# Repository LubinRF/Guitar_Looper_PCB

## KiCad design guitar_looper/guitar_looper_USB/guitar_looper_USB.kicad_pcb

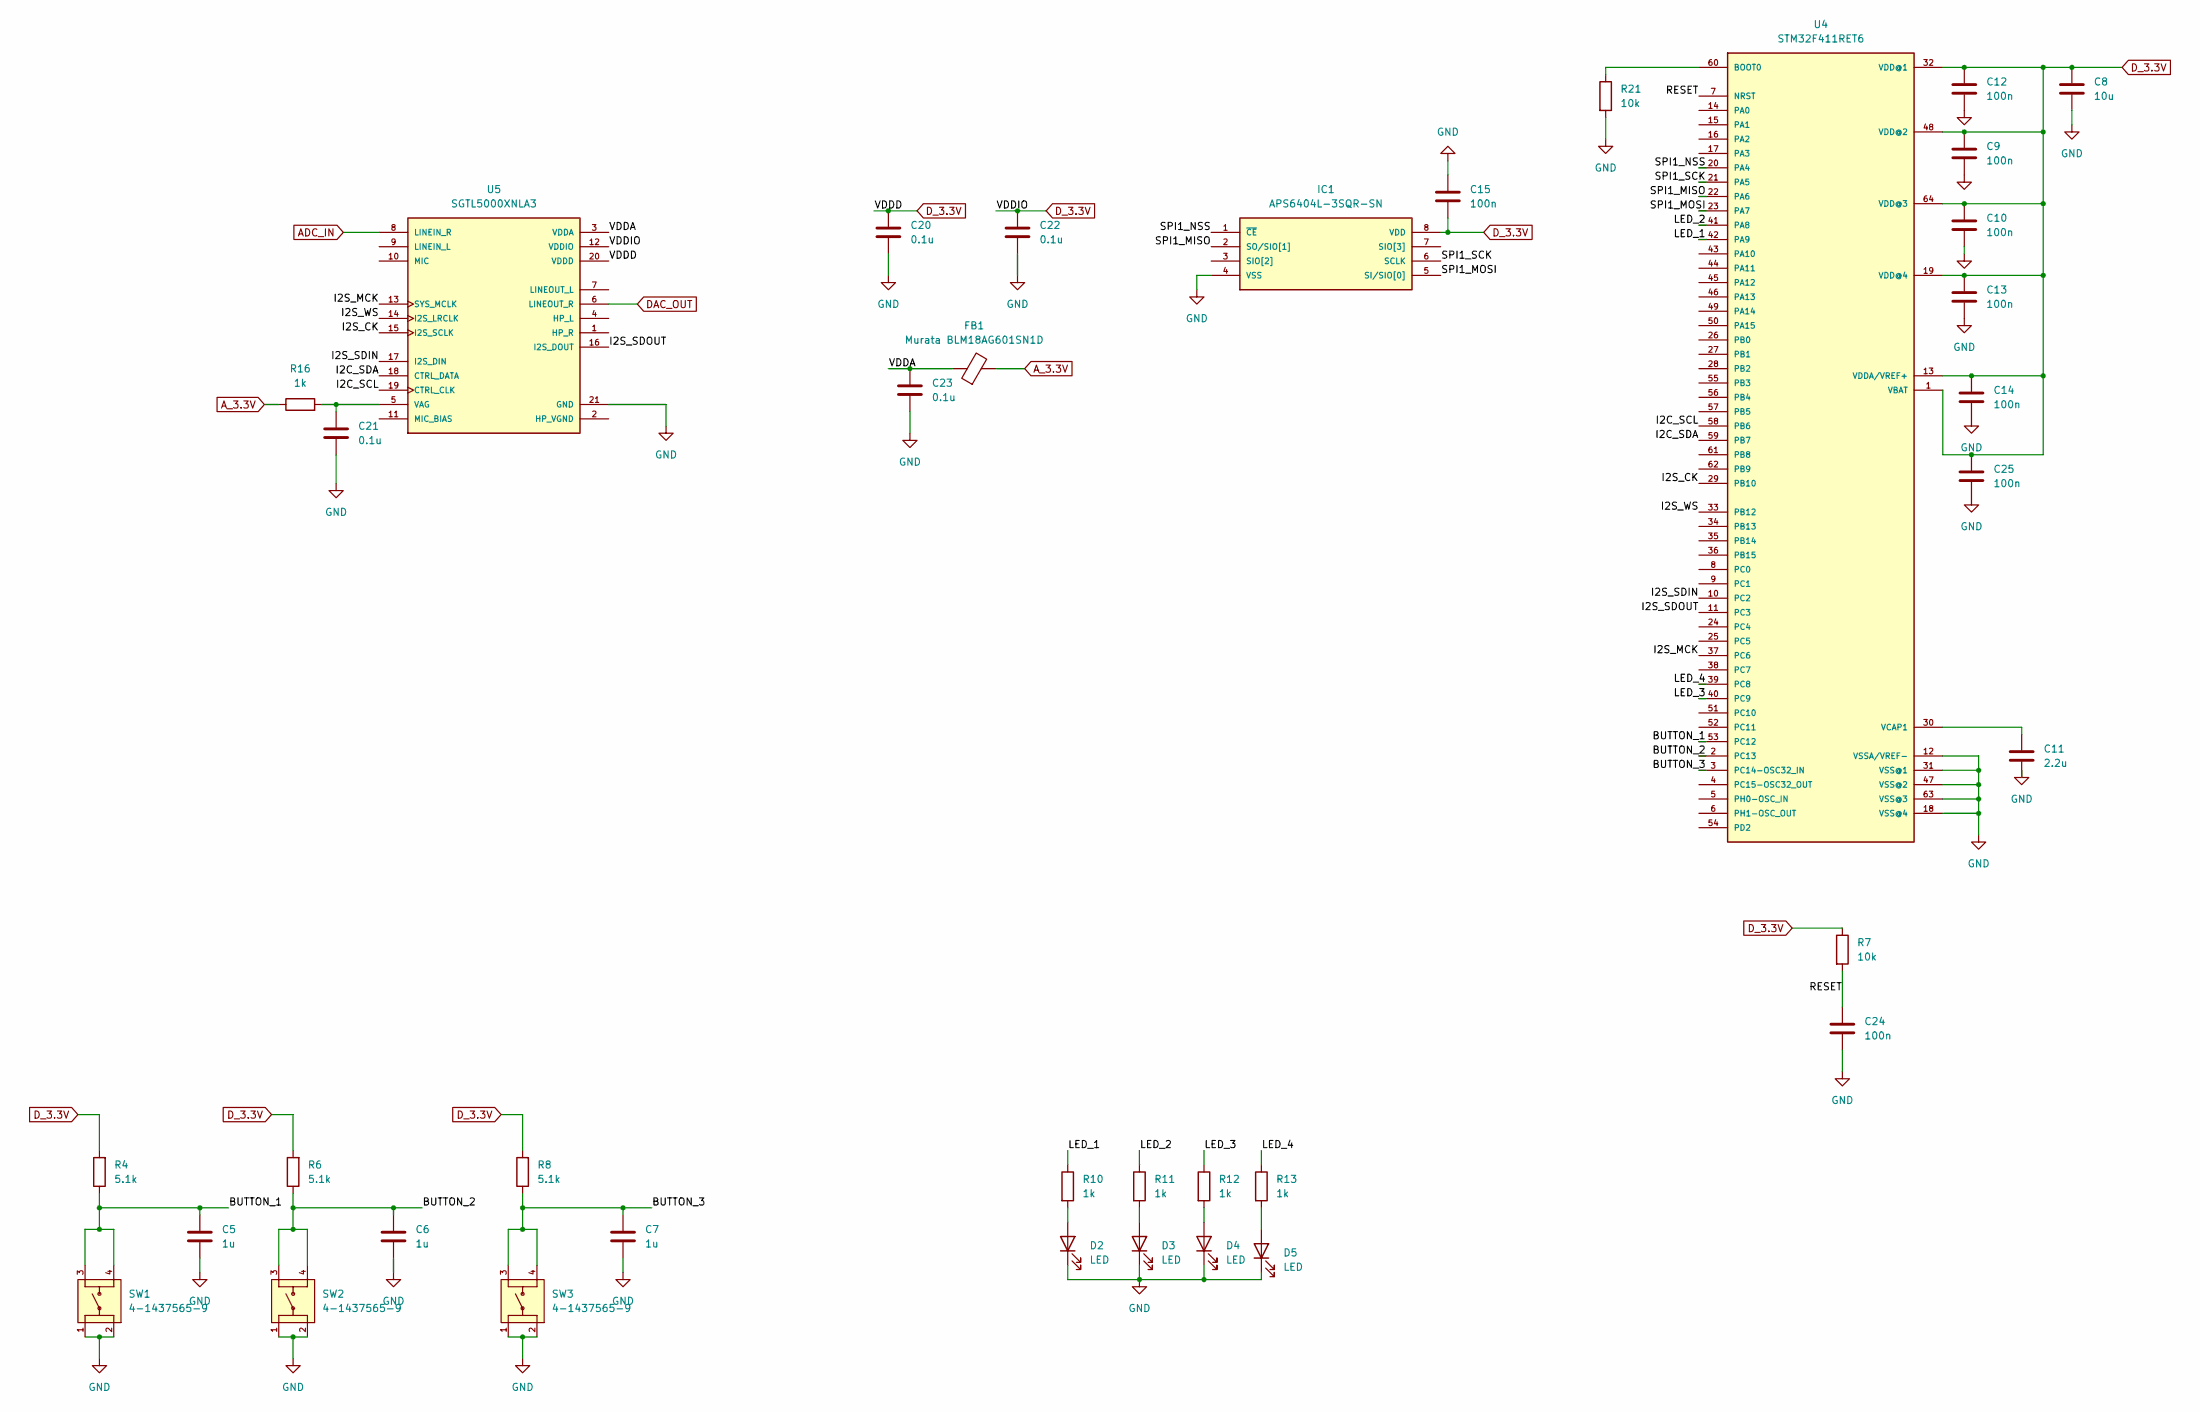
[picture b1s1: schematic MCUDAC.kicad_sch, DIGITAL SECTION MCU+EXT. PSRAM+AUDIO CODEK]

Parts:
C5, C6, C7: 1u; C_0805_2012Metric
C8: 10u; C_0805_2012Metric
C9, C10, C12, C13, C14, C15, C24, C25: 100n; C_0603_1608Metric
C11: 2.2u; C_0805_2012Metric
C20, C21, C22, C23: 0.1u; C_0603_1608Metric
D2, D3, D4, D5: LED; C_0805_2012Metric
FB1: Murata BLM18AG601SN1D; C_0805_2012Metric
IC1: APS6404L-3SQR-SN; SOIC-8_3.9x4.9mm_P1.27mm; MOUSER_PART_NUMBER 878-APS6404L-3SQR-SN
R4, R6, R8: 5.1k; C_0805_2012Metric
R7: 10k; C_0603_1608Metric
R10, R11, R12, R13: 1k; C_0805_2012Metric
R16: 1k; C_0603_1608Metric
R21: 10k; C_0805_2012Metric
SW1, SW2, SW3: 4-1437565-9; SW_Push_2P1T_Toggle_CK_PVA1xxH4xxxxxxV2; PARTREV V
U4: STM32F411RET6; LQFP-64_10x10mm_P0.5mm
U5: SGTL5000XNLA3; QFN-20-1EP_3x3mm_P0.4mm_EP1.65x1.65mm

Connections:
/MCU+DAC/BUTTON_1: C5.1, R4.1, SW1.3, SW1.4, U4.53 (PC12)
/MCU+DAC/BUTTON_2: C6.1, R6.1, SW2.3, SW2.4, U4.2 (PC13)
/MCU+DAC/BUTTON_3: C7.1, R8.1, SW3.3, SW3.4, U4.3 (PC14-OSC32_IN)
/MCU+DAC/I2C_SCL: U4.58 (PB6), U5.19 (CTRL_CLK)
/MCU+DAC/I2C_SDA: U4.59 (PB7), U5.18 (CTRL_DATA)
/MCU+DAC/I2S_CK: U4.29 (PB10), U5.15 (I2S_SCLK)
/MCU+DAC/I2S_MCK: U4.37 (PC6), U5.13 (SYS_MCLK)
/MCU+DAC/I2S_SDIN: U4.10 (PC2), U5.17 (I2S_DIN)
/MCU+DAC/I2S_SDOUT: U4.11 (PC3), U5.16 (I2S_DOUT)
/MCU+DAC/I2S_WS: U4.33 (PB12), U5.14 (I2S_LRCLK)
/MCU+DAC/LED_1: R10.1, U4.42 (PA9)
/MCU+DAC/LED_2: R11.1, U4.41 (PA8)
/MCU+DAC/LED_3: R12.1, U4.40 (PC9)
/MCU+DAC/LED_4: R13.1, U4.39 (PC8)
/MCU+DAC/RESET: C24.1, R7.2, U4.7 (NRST)
/MCU+DAC/SPI1_MISO: IC1.2 (SO/SIO[1]), U4.22 (PA6)
/MCU+DAC/SPI1_MOSI: IC1.5 (SI/SIO[0]), U4.23 (PA7)
/MCU+DAC/SPI1_NSS: IC1.1 (~CE), U4.20 (PA4)
/MCU+DAC/SPI1_SCK: IC1.6 (SCLK), U4.21 (PA5)
/MCU+DAC/VDDA: C23.1, FB1.1, U5.3 (VDDA)
ADC_IN: U5.8 (LINEIN_R); also elsewhere on the board
A_3.3V: FB1.2, R16.1; also elsewhere on the board
DAC_OUT: U5.6 (LINEOUT_R); also elsewhere on the board
D_3.3V: C8.2, C9.1, C10.1, C12.1, C13.2, C14.2, C15.2, C20.1, C22.1, C25.2, IC1.8 (VDD), R4.2, R6.2, R7.1, R8.2, U4.1 (VBAT), U4.13 (VDDA/VREF+), U4.19 (VDD@4), U4.32 (VDD@1), U4.48 (VDD@2), U4.64 (VDD@3), U5.12 (VDDIO), U5.20 (VDDD); also elsewhere on the board
GND: C5.2, C6.2, C7.2, C8.1, C9.2, C10.2, C11.1, C12.2, C13.1, C14.1, C15.1, C20.2, C21.2, C22.2, C23.2, C24.2, C25.1, D2.1 (K), D3.1 (K), D4.1 (K), D5.1 (K), IC1.4 (VSS), R21.2, SW1.1, SW1.2, SW2.1, SW2.2, SW3.1, SW3.2, U4.12 (VSSA/VREF-), U4.18 (VSS@4), U4.31 (VSS@1), U4.47 (VSS@2), U4.63 (VSS@3), U5.21 (GND); also elsewhere on the board
unnamed: D2.2 (A), R10.2
unnamed: D3.2 (A), R11.2
unnamed: D4.2 (A), R12.2
unnamed: D5.2 (A), R13.2
unnamed: R21.1, U4.60 (BOOT0)
unnamed: C11.2, U4.30 (VCAP1)
unnamed: C21.1, R16.2, U5.5 (VAG)

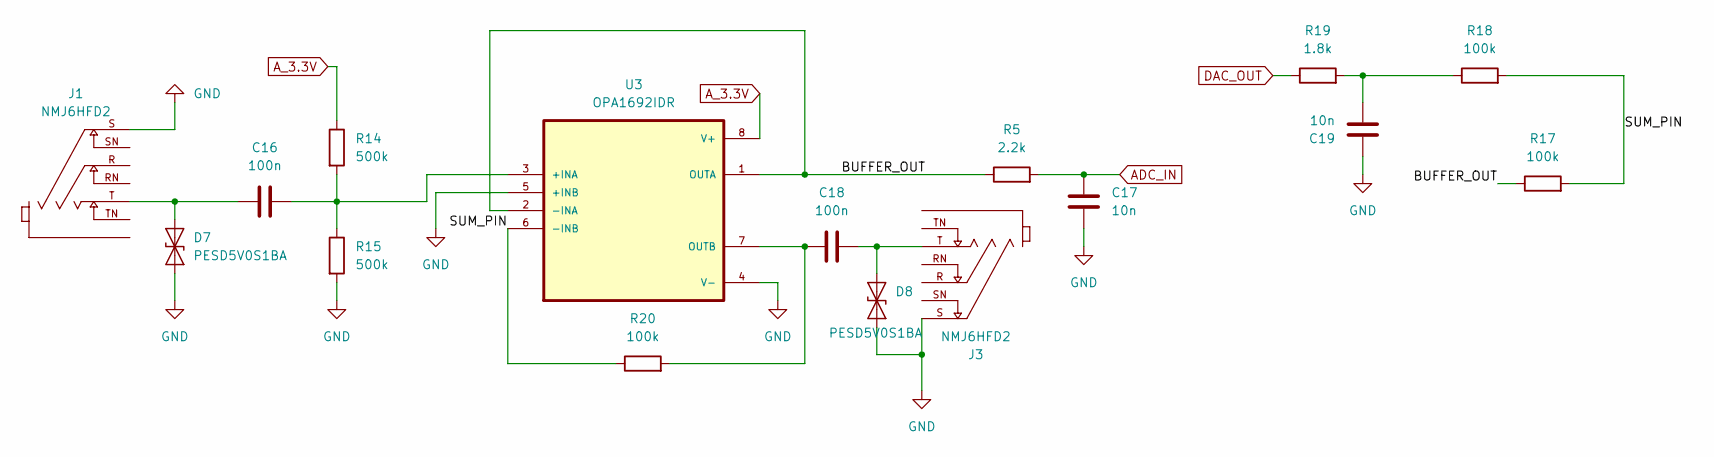
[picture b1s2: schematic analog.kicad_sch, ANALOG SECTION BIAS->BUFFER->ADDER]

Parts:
C16, C18: 100n; C_0805_2012Metric
C17, C19: 10n; C_0805_2012Metric
D7, D8: PESD5V0S1BA; D_SOD-323
J1, J3: NMJ6HFD2; Jack_6.35mm_Neutrik_NMJ6HFD2-AU_Horizontal; PARTREV 26.02.2021
R5: 2.2k; C_0805_2012Metric
R14, R15: 500k; C_0603_1608Metric
R17, R18, R20: 100k; C_0805_2012Metric
R19: 1.8k; C_0805_2012Metric
U3: OPA1692IDR; SOIC-8_3.9x4.9mm_P1.27mm

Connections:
/analog/BUFFER_OUT: R5.1, R17.1, U3.1 (OUTA), U3.2 (-INA)
/analog/SUM_PIN: R17.2, R18.2, R20.1, U3.6 (-INB)
ADC_IN: C17.1, R5.2; also elsewhere on the board
A_3.3V: R14.1, U3.8 (V+); also elsewhere on the board
DAC_OUT: R19.1; also elsewhere on the board
GND: C17.2, C19.1, D7.1 (A1), D8.1 (A1), J1.S, J3.S, R15.2, U3.4 (V-), U3.5 (+INB); also elsewhere on the board
unnamed: C19.2, R18.1, R19.2
unnamed: C16.1, D7.2 (A2), J1.T
unnamed: C18.2, D8.2 (A2), J3.T
unnamed: C16.2, R14.2, R15.1, U3.3 (+INA)
unnamed: C18.1, R20.2, U3.7 (OUTB)

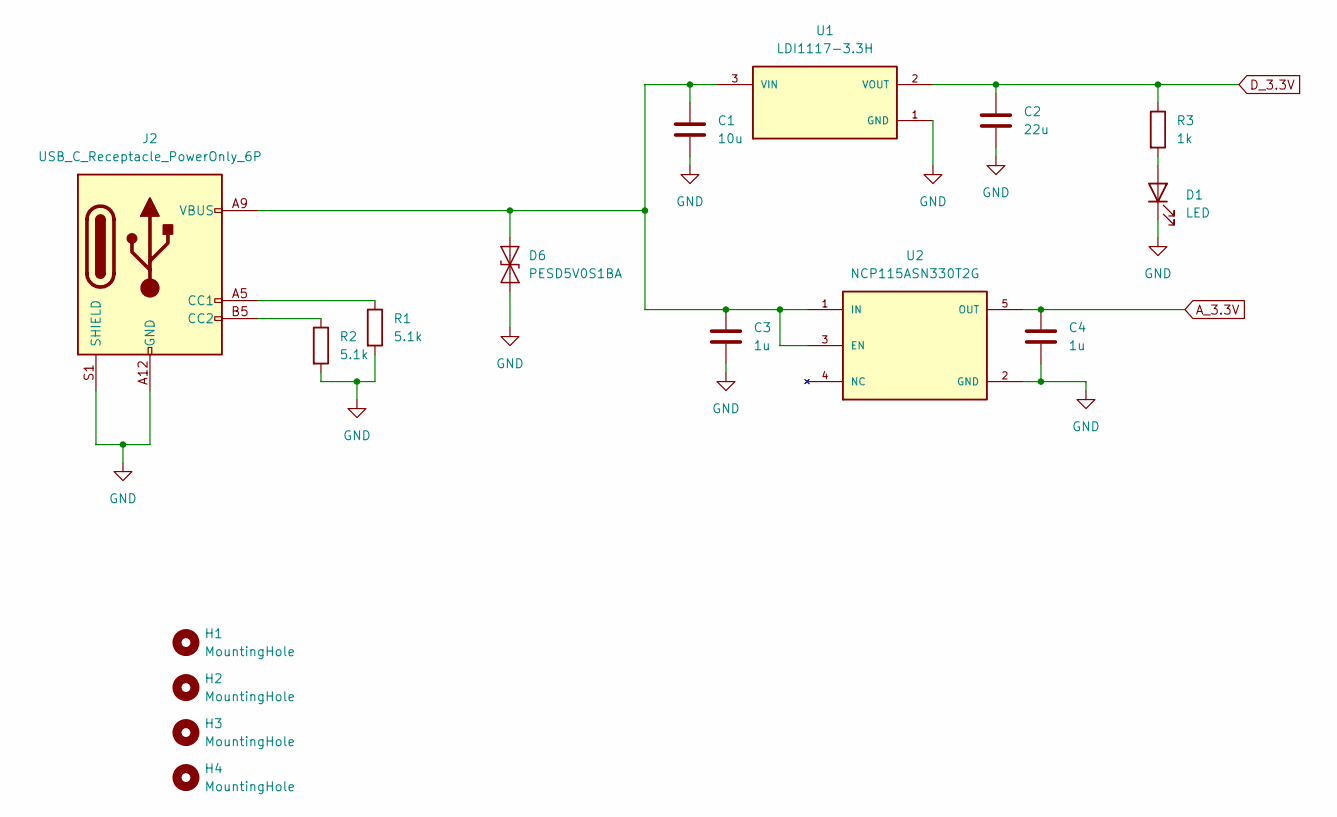
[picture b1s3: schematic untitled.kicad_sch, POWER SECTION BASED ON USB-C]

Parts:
C1: 10u; C_1206_3216Metric
C2: 22u; C_1206_3216Metric
C3, C4: 1u; C_0805_2012Metric
D1: LED; C_0805_2012Metric
D6: PESD5V0S1BA; D_SOD-323
H1, H2, H3, H4: MountingHole; MountingHole_2.2mm_M2
J2: USB_C_Receptacle_PowerOnly_6P; USB_C_Receptacle_GCT_USB4135-GF-A_6P_TopMnt_Horizontal
R1, R2: 5.1k; C_0805_2012Metric
R3: 1k; C_0805_2012Metric
U1: LDI1117-3.3H; SOT230P700X165-4N; PARTREV N/A
U2: NCP115ASN330T2G; TSOP-5_1.65x3.05mm_P0.95mm; PARTREV 5

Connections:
A_3.3V: C4.1, U2.5 (OUT); also elsewhere on the board
D_3.3V: C2.1, R3.1, U1.2 (VOUT), U1.4 (VOUT); also elsewhere on the board
GND: C1.2, C2.2, C3.2, C4.2, D1.1 (K), D6.1 (A1), J2.A12 (GND), J2.B12 (GND), J2.S1 (SHIELD), R1.2, R2.2, U1.1 (GND), U2.2 (GND); also elsewhere on the board
unnamed: D1.2 (A), R3.2
unnamed: C1.1, C3.1, D6.2 (A2), J2.A9 (VBUS), J2.B9 (VBUS), U1.3 (VIN), U2.1 (IN), U2.3 (EN)
unnamed: J2.A5 (CC1), R1.1
unnamed: J2.B5 (CC2), R2.1

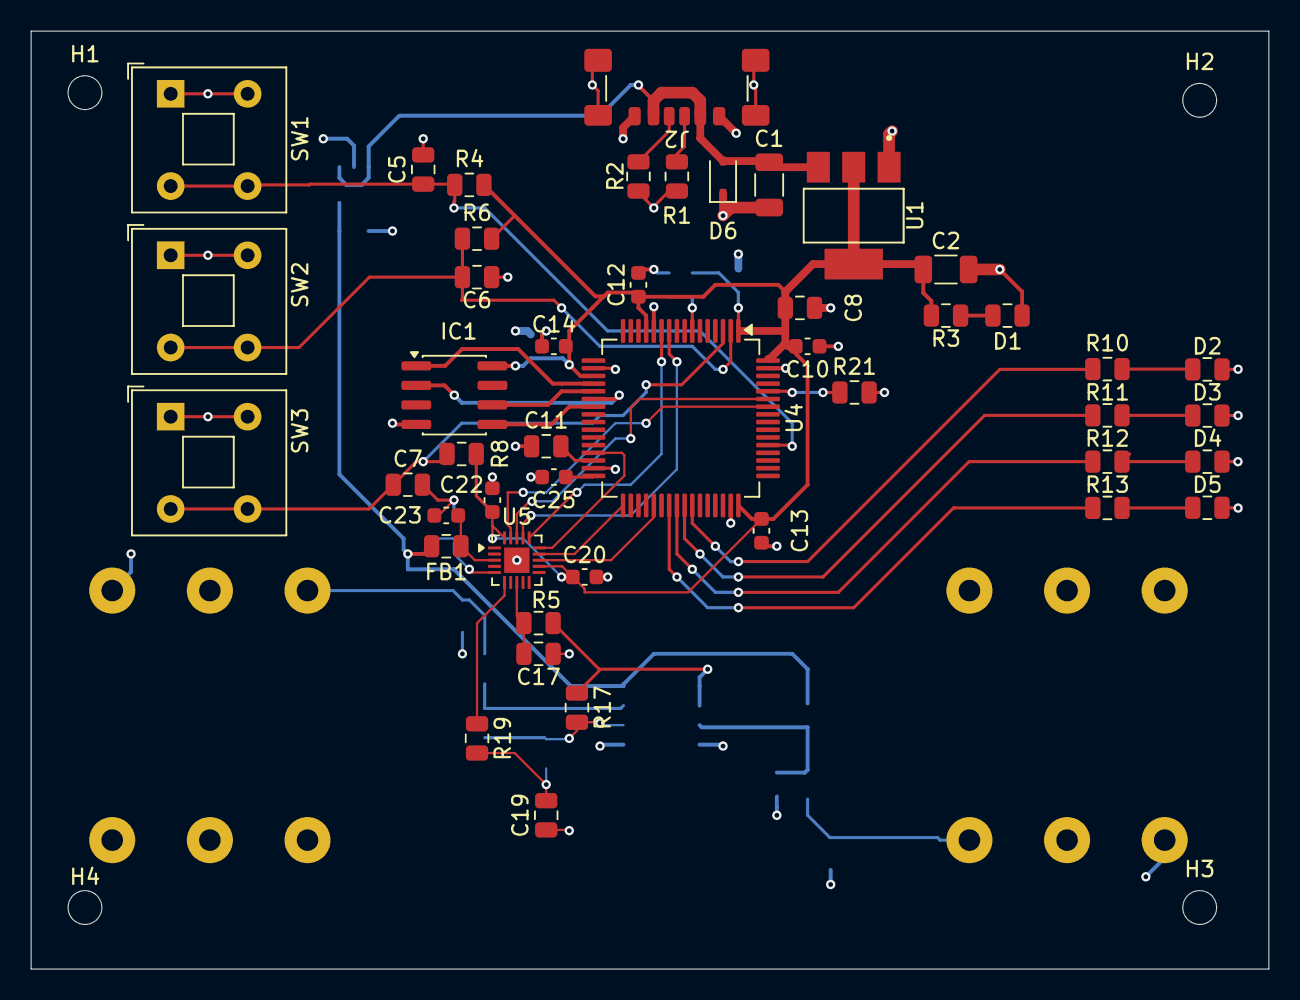
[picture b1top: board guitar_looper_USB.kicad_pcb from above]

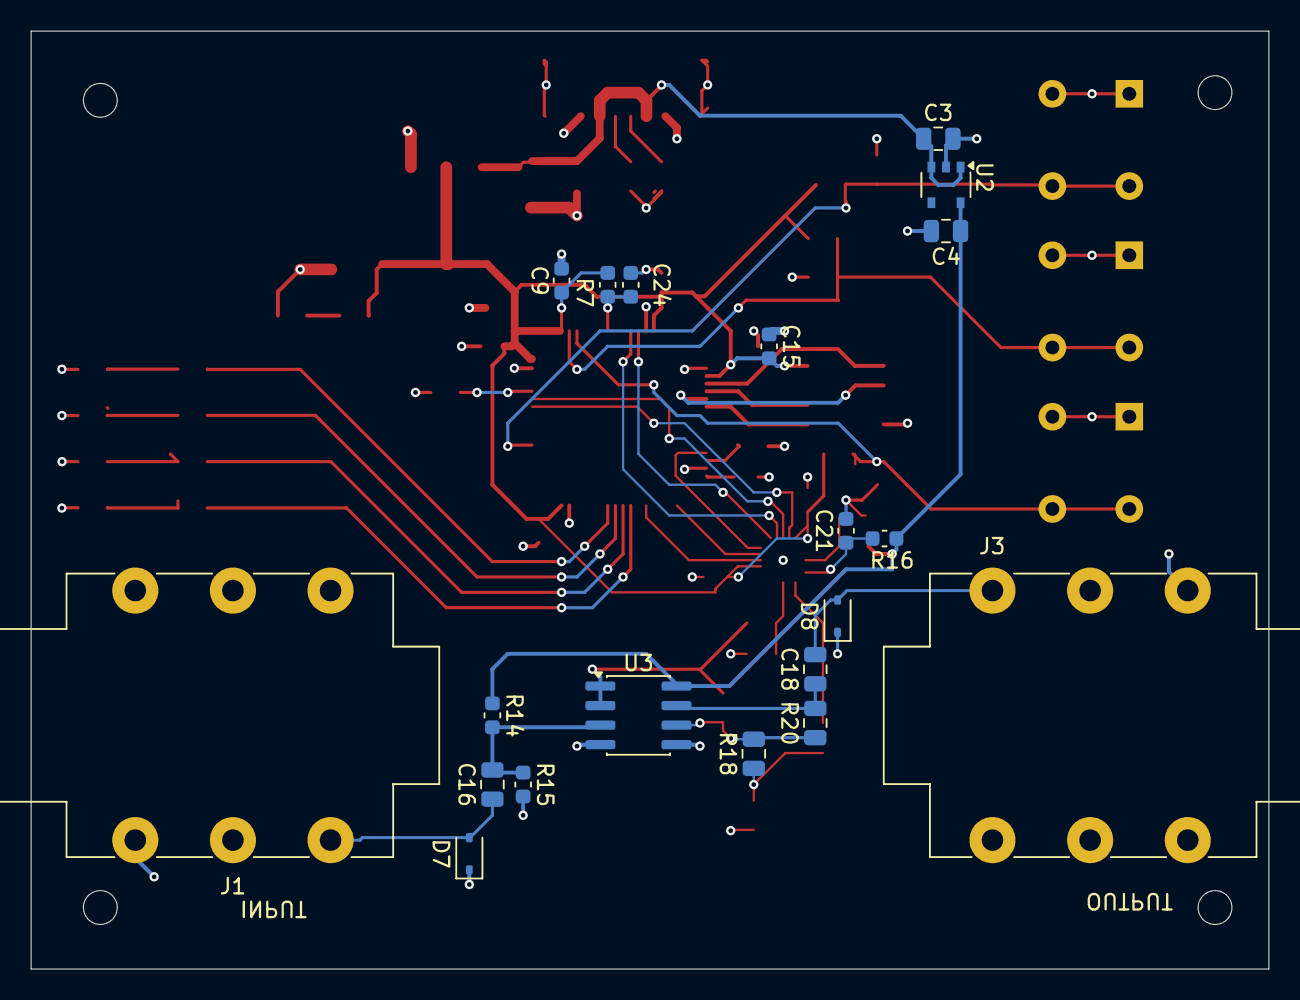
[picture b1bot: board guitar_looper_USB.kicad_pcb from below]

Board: 4 copper layers, 80.5 x 61.0 mm, 70 parts (20 on the bottom side), 43 nets.

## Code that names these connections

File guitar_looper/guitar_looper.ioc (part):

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Mcu.Name=STM32F411R(C-E)Tx
Mcu.Package=LQFP64
Mcu.UserName=STM32F411RETx
PA13.Mode=Serial_Wire
PA13.Signal=SYS_JTMS-SWDIO
PA14.Mode=Serial_Wire
PA14.Signal=SYS_JTCK-SWCLK
PA4.Mode=NSS_Signal_Hard_Output
PA4.Signal=SPI1_NSS
PA5.Mode=Full_Duplex_Master
PA5.Signal=SPI1_SCK
PA6.Mode=Full_Duplex_Master
PA6.Signal=SPI1_MISO
PA7.Mode=Full_Duplex_Master
PA7.Signal=SPI1_MOSI
PA8.GPIOParameters=GPIO_Label
PA8.GPIO_Label=LED_2
PA8.Signal=GPIO_Output
PA9.GPIOParameters=GPIO_Label
PA9.GPIO_Label=LED_1
PA9.Signal=GPIO_Output
PB10.Mode=Full_Duplex_Master
PB10.Signal=I2S2_CK
PB12.Mode=Full_Duplex_Master
PB12.Signal=I2S2_WS
PB6.Mode=I2C
PB6.Signal=I2C1_SCL
PB7.Mode=I2C
PB7.Signal=I2C1_SDA
PC12.GPIOParameters=GPIO_Label
PC12.GPIO_Label=BUTTON_1
PC12.Signal=GPIO_Input
PC13-ANTI_TAMP.GPIOParameters=GPIO_Label
PC13-ANTI_TAMP.GPIO_Label=BUTTON_2
PC13-ANTI_TAMP.Signal=GPIO_Input
PC14-OSC32_IN.GPIOParameters=GPIO_Label
PC14-OSC32_IN.GPIO_Label=BUTTON_3
PC14-OSC32_IN.Signal=GPIO_Input
PC2.Mode=Full_Duplex_Master
PC2.Signal=I2S2_ext_SD
PC3.Mode=Full_Duplex_Master
PC3.Signal=I2S2_SD
PC6.Mode=Master_Clock_Activated
PC6.Signal=I2S2_MCK
PC8.GPIOParameters=GPIO_Label
PC8.GPIO_Label=LED_4
PC8.Signal=GPIO_Output
PC9.GPIOParameters=GPIO_Label
PC9.GPIO_Label=LED_3
PC9.Signal=GPIO_Output
RCC.HSE_VALUE=25000000
RCC.SYSCLKFreq_VALUE=16000000
board=custom

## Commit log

2026-06-30 name change
